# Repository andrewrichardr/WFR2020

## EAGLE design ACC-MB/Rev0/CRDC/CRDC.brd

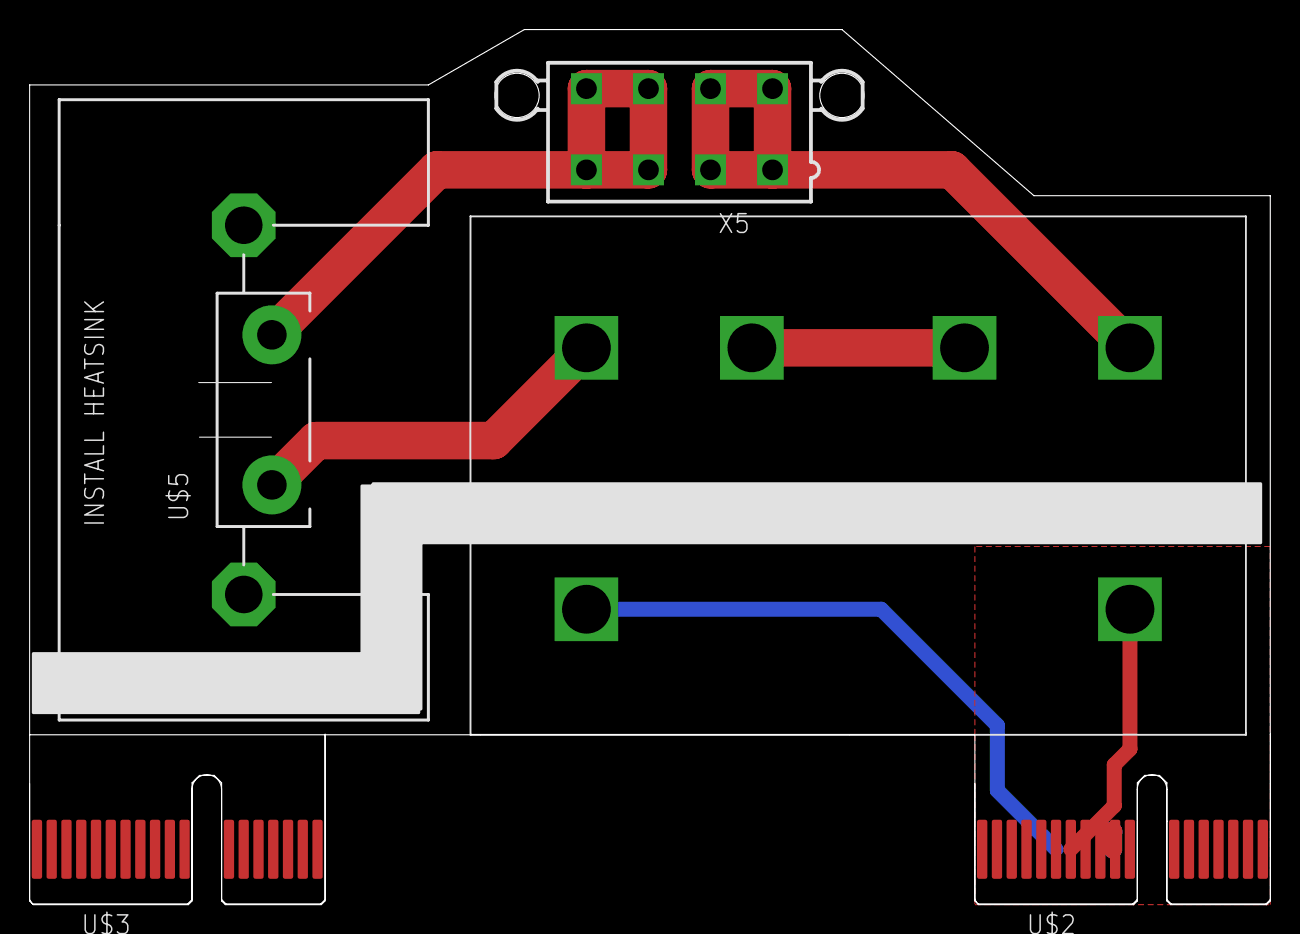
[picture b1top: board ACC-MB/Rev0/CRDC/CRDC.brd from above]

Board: 2 copper layers, 84.0 x 59.2 mm, 5 parts (0 on the bottom side), 6 nets.

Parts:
U$1: G7L
U$2, U$3: PCIE-36-EDGE; PCI-E_SLOT_36
U$5: TO247RESISTORHEATINK; _CUSTOM_TO-247-2V
X5: 5566-8

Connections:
HV+_WET: U$5.2, X5.3, X5.4, X5.7, X5.8
unnamed: U$1.1, U$2.A1, U$2.A2, U$2.A3, U$2.A4, U$2.A5, U$2.A6, U$2.A7, U$2.A8, U$2.A9, U$2.A10, U$2.A11, U$2.A12, U$2.A13, U$2.A14, U$2.A15, U$2.A16, U$2.A17, U$2.A18
unnamed: U$1.0, U$2.B1, U$2.B2, U$2.B3, U$2.B4, U$2.B5, U$2.B6, U$2.B7, U$2.B8, U$2.B9, U$2.B10, U$2.B11, U$2.B12, U$2.B13, U$2.B14, U$2.B15, U$2.B16, U$2.B17, U$2.B18
unnamed: U$1.8, U$5.1
unnamed: U$1.4, U$1.6
V+: U$1.2, X5.1, X5.2, X5.5, X5.6

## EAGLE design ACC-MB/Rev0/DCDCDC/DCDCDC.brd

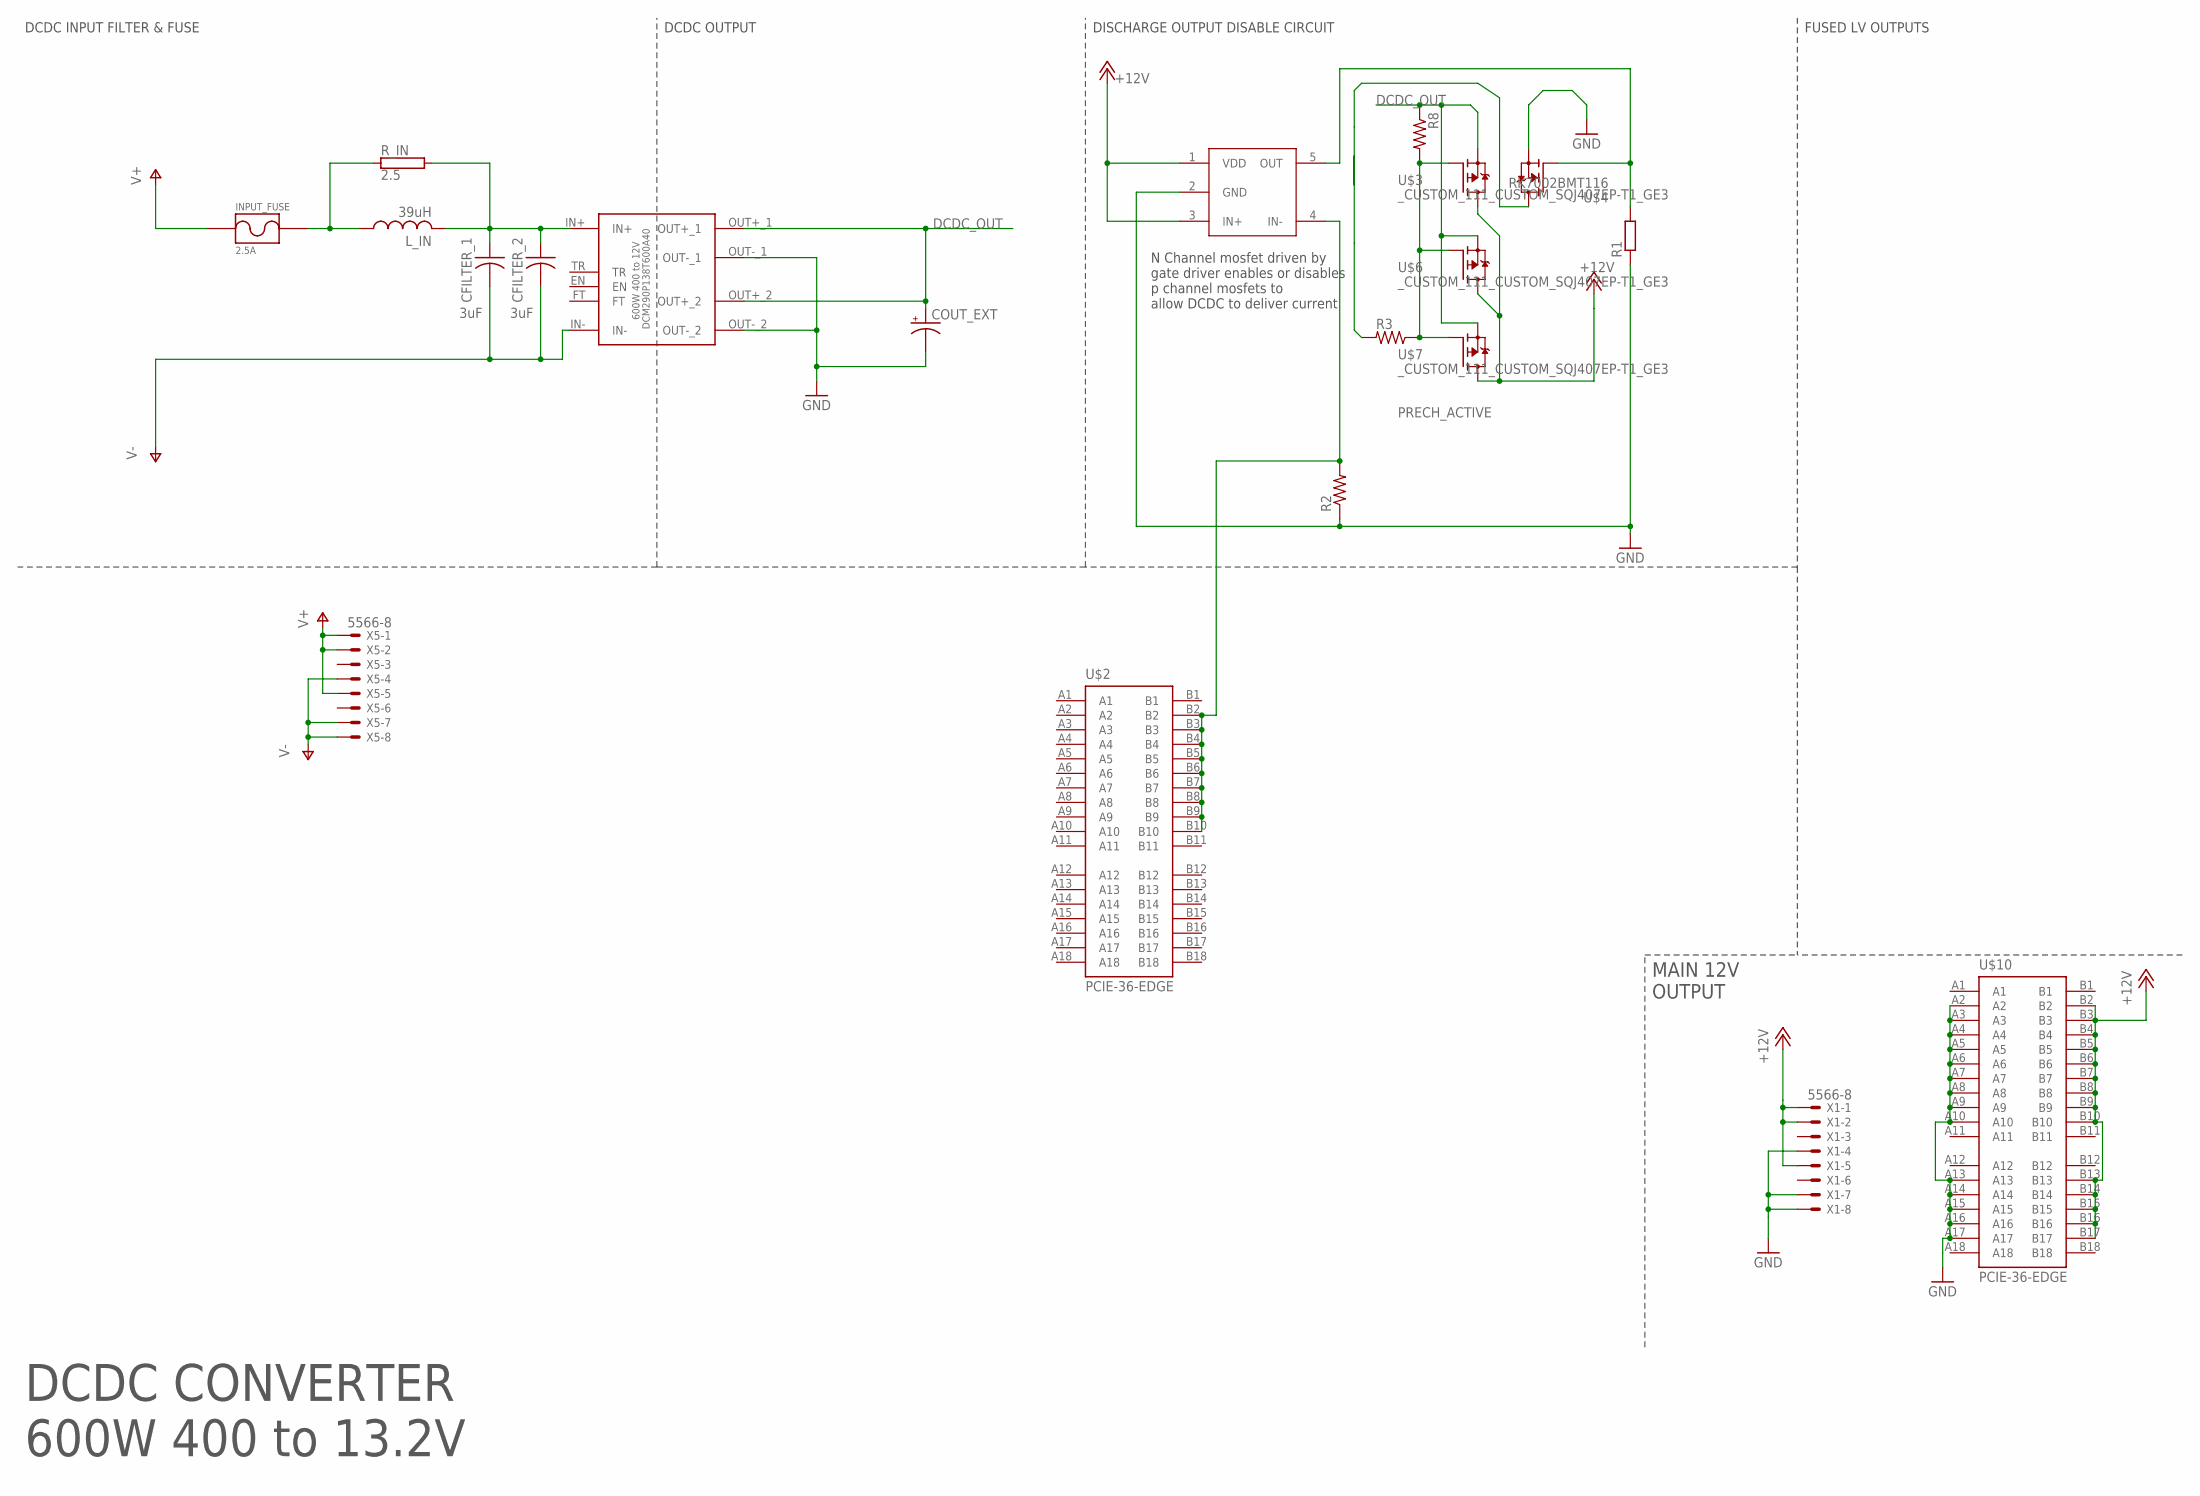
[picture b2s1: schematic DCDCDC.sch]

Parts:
CFILTER_1, CFILTER_2: 3uF; CERALINK_FA3
COUT_EXT: CPOL-USE7.5-16; E7,5-16
DCM290P138T600A40: 600W 400 to 12V; VICOR_CHIP_HEATSINK
INPUT_FUSE: 2.5A; _CUSTOM_PARTS_LF_885
L_IN: 39uH; L_1510_NONSTANDARD
R1: R-EU_R0805; R0805
R2, R3, R8: R-US_R0805; R0805
R_IN: 2.5; TO-247-2V
U$2, U$10: PCIE-36-EDGE; PCI-E_SLOT_36
U$3, U$6, U$7: _CUSTOM_111_CUSTOM_SQJ407EP-T1_GE3; _CUSTOM_111_CUSTOM_TRANS_SIRA90DP-T1-GE3
U$4: RK7002BMT116; SOT23
U$5: UCC27511AQDBVRQ1; SOT23-5L
X1, X5: 5566-8

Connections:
+12V: U$3.5 (D), U$5.1 (VDD), U$5.3 (IN+), U$6.5 (D), U$7.5 (D), U$10.B2, U$10.B3, U$10.B4, U$10.B5, U$10.B6, U$10.B7, U$10.B8, U$10.B9, U$10.B10, U$10.B13, U$10.B14, U$10.B15, U$10.B16, U$10.B17
DCDC_OUT: COUT_EXT.+, DCM290P138T600A40.OUT+_1, DCM290P138T600A40.OUT+_2, R8.1, U$3.1 (S), U$3.2 (S), U$3.3 (S), U$6.1 (S), U$6.2 (S), U$6.3 (S), U$7.1 (S), U$7.2 (S), U$7.3 (S)
GND: COUT_EXT.-, DCM290P138T600A40.OUT-_1, DCM290P138T600A40.OUT-_2, R1.1, R2.1, U$4.2 (S), U$5.2 (GND), U$10.A2, U$10.A3, U$10.A4, U$10.A5, U$10.A6, U$10.A7, U$10.A8, U$10.A9, U$10.A10, U$10.A13, U$10.A14, U$10.A15, U$10.A16, U$10.A17
unnamed: R3.1, R8.2, U$3.4 (G), U$6.4 (G), U$7.4 (G)
unnamed: R1.2, U$4.1 (G), U$5.5 (OUT)
unnamed: CFILTER_1.P$1 (1), CFILTER_2.P$1 (1), DCM290P138T600A40.IN+, L_IN.P$2 (2), R_IN.2
unnamed: R3.2, U$4.3 (D)
unnamed: X1.1, X1.2, X1.5
unnamed: X1.4, X1.7, X1.8
PRECH_ACTIVE: R2.2, U$2.B2, U$2.B3, U$2.B4, U$2.B5, U$2.B6, U$2.B7, U$2.B8, U$2.B9, U$2.B10, U$5.4 (IN-)
V+: INPUT_FUSE.P$1, X5.1, X5.2, X5.5
V+_FUSED: INPUT_FUSE.P$2, L_IN.P$1 (1), R_IN.1
V-: CFILTER_1.P$2 (2), CFILTER_2.P$2 (2), DCM290P138T600A40.IN-, X5.4, X5.7, X5.8

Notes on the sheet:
DCDC CONVERTER 600W 400 to 13.2V
DISCHARGE OUTPUT DISABLE CIRCUIT
FUSED LV OUTPUTS
MAIN 12V OUTPUT
DCDC OUTPUT
DCDC INPUT FILTER & FUSE
N Channel mosfet driven by gate driver enables or disables p channel mosfets to allow DCDC to deliver current

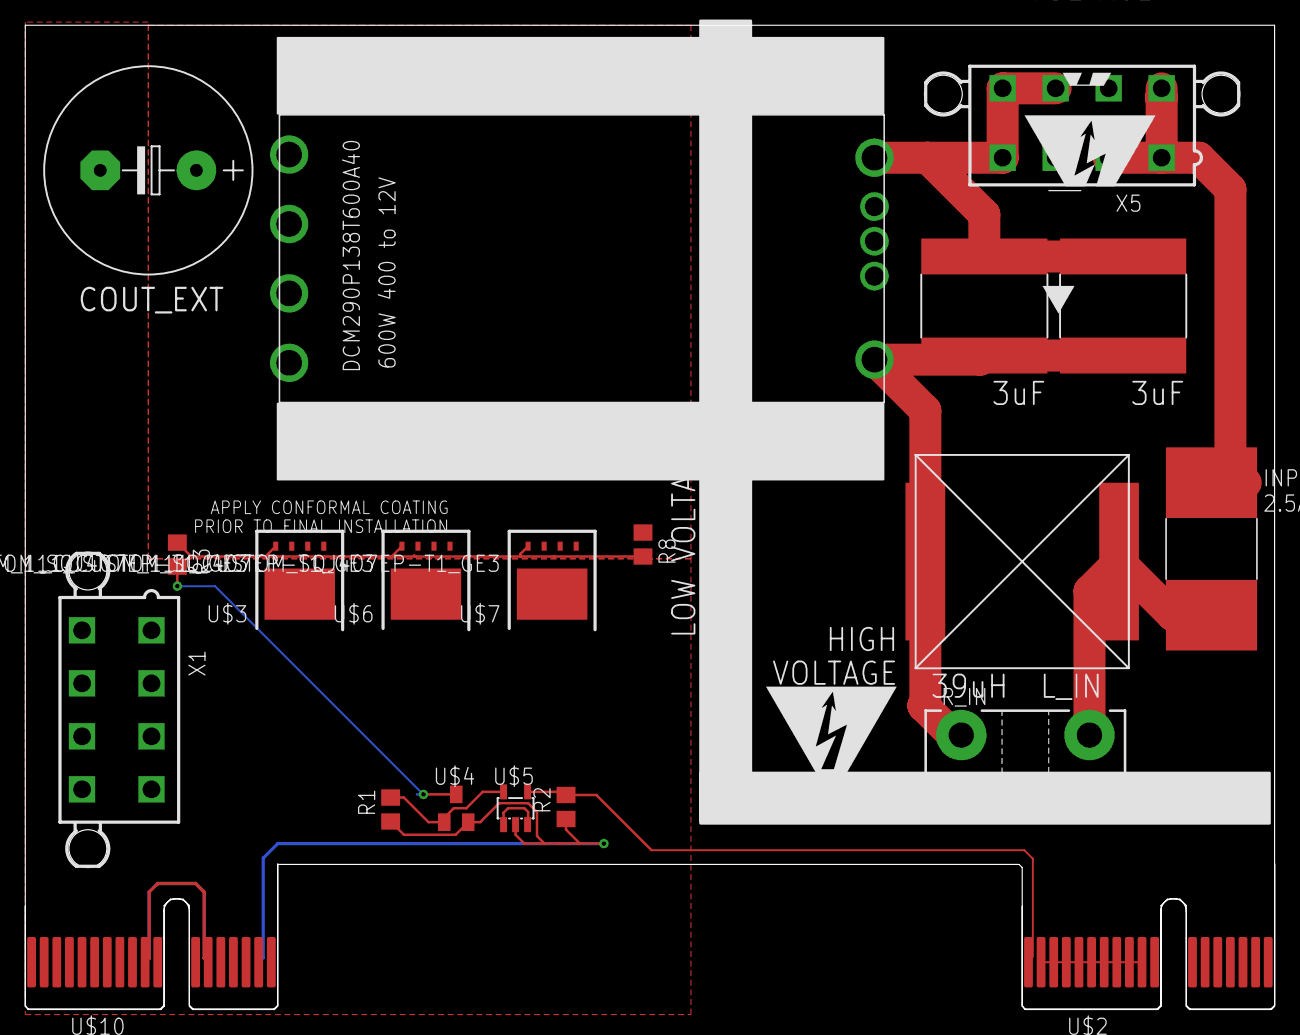
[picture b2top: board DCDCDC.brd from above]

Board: 2 copper layers, 99.0 x 78.0 mm, 20 parts (0 on the bottom side), 13 nets.

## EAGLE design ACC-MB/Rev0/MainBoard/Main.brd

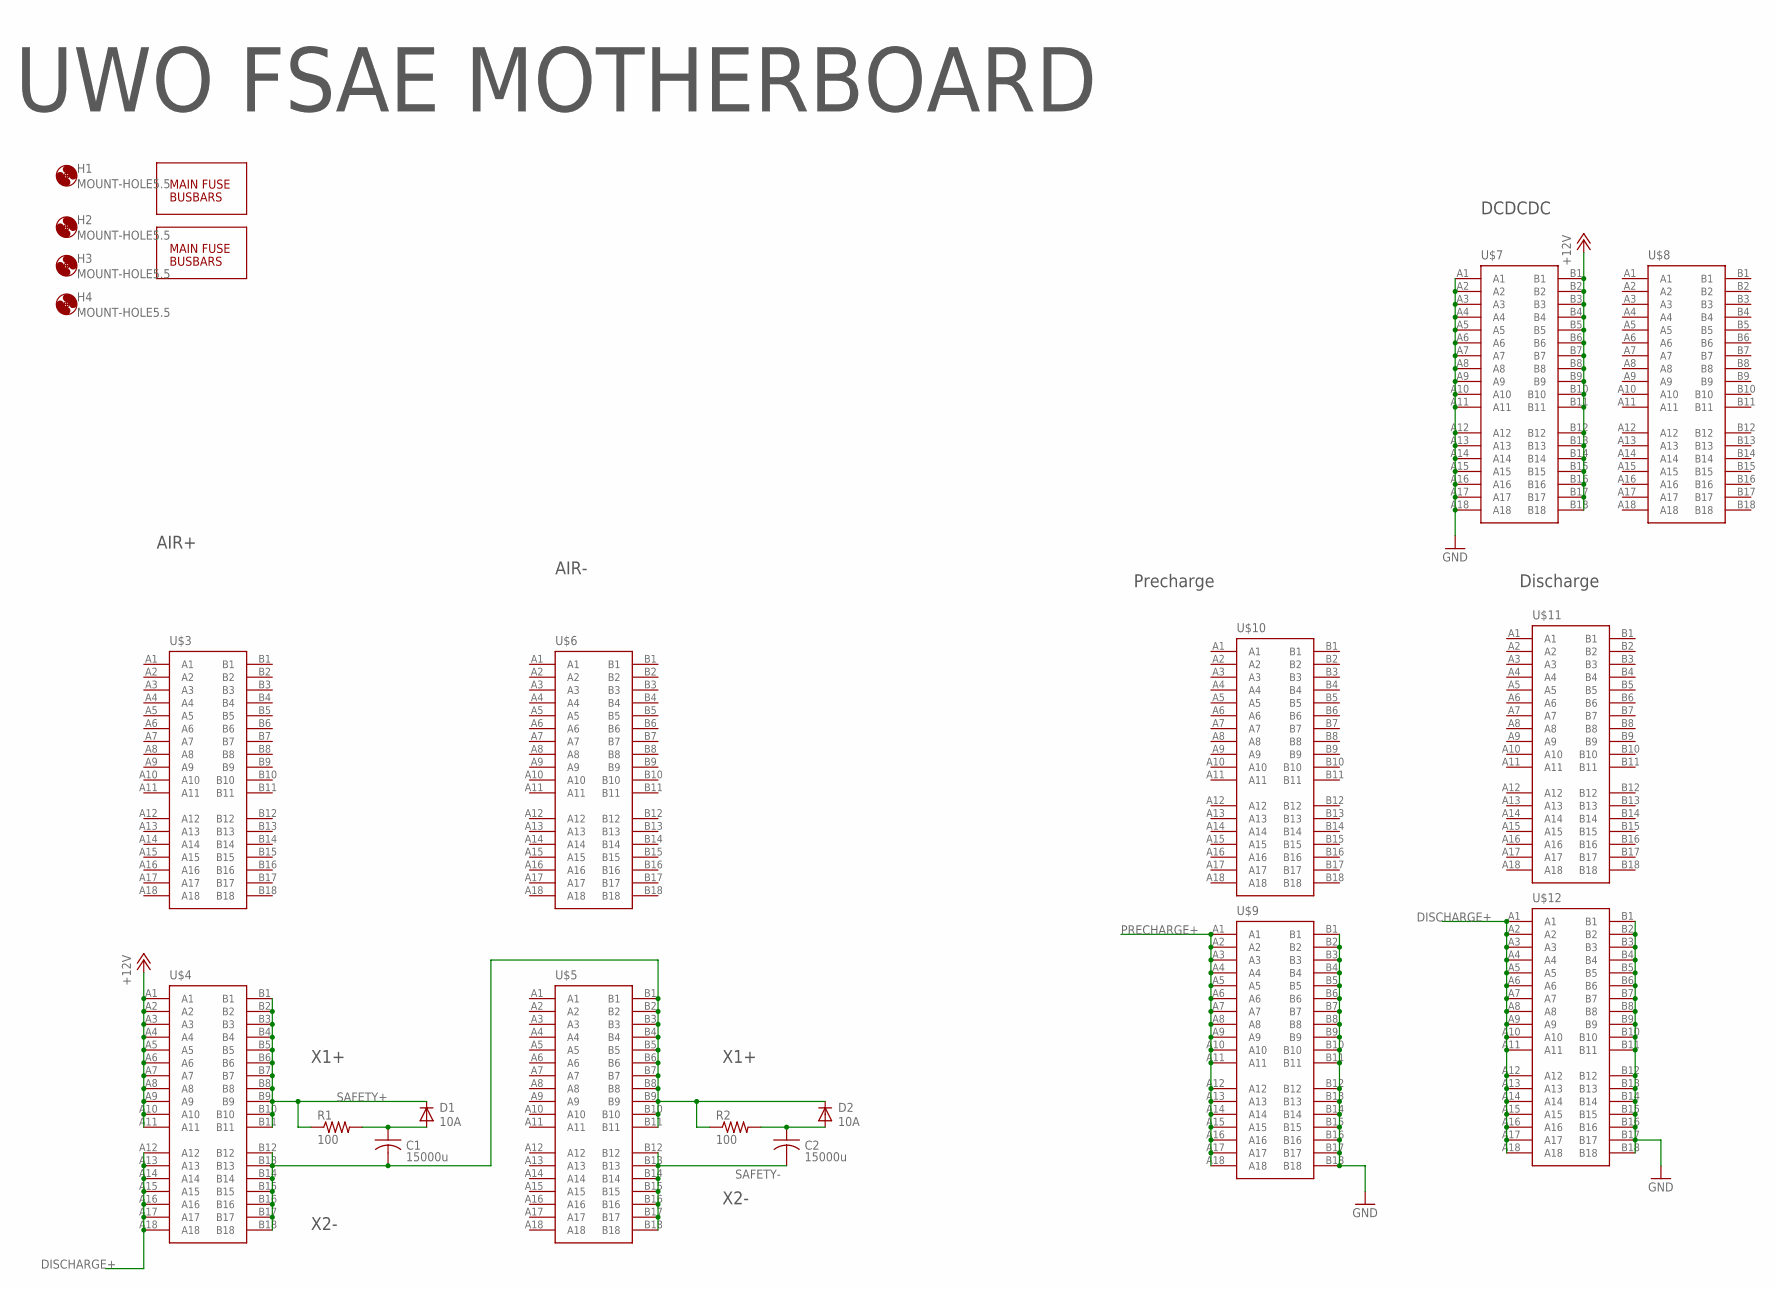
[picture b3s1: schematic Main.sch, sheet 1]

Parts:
C1, C2: 15000u; CAPPRD750W65D1800H3700B
D1, D2: 10A; DIOAD1570W120L850D500B
H1, H2, H3, H4: MOUNT-HOLE5.5; 5,5
R1, R2: 100; RESAD976W63L650D250B
U$1, U$2: FUSE_HOLDER
U$3, U$4, U$5, U$6, U$7, U$8, U$9, U$10, U$11, U$12: PCIE-36-CONN; PCI-E-36-CONN

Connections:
+12V: U$4.A1, U$4.A2, U$4.A3, U$4.A4, U$4.A5, U$4.A6, U$4.A7, U$4.A8, U$4.A9, U$4.A10, U$4.A11, U$7.B1, U$7.B2, U$7.B3, U$7.B4, U$7.B5, U$7.B6, U$7.B7, U$7.B8, U$7.B9, U$7.B10, U$7.B11, U$7.B12, U$7.B13, U$7.B14, U$7.B15, U$7.B16, U$7.B17, U$7.B18; also elsewhere on the board
DISCHARGE+: U$4.A12, U$4.A13, U$4.A14, U$4.A15, U$4.A16, U$4.A17, U$4.A18, U$12.A1, U$12.A2, U$12.A3, U$12.A4, U$12.A5, U$12.A6, U$12.A7, U$12.A8, U$12.A9, U$12.A10, U$12.A11, U$12.A12, U$12.A13, U$12.A14, U$12.A15, U$12.A16, U$12.A17, U$12.A18
GND: U$7.A1, U$7.A2, U$7.A3, U$7.A4, U$7.A5, U$7.A6, U$7.A7, U$7.A8, U$7.A9, U$7.A10, U$7.A11, U$7.A12, U$7.A13, U$7.A14, U$7.A15, U$7.A16, U$7.A17, U$7.A18, U$9.B1, U$9.B2, U$9.B3, U$9.B4, U$9.B5, U$9.B6, U$9.B7, U$9.B8, U$9.B9, U$9.B10, U$9.B11, U$9.B12, U$9.B13, U$9.B14, U$9.B15, U$9.B16, U$9.B17, U$9.B18, U$12.B1, U$12.B2, U$12.B3, U$12.B4, U$12.B5, U$12.B6, U$12.B7, U$12.B8, U$12.B9, U$12.B10, U$12.B11, U$12.B12, U$12.B13, U$12.B14, U$12.B15, U$12.B16, U$12.B17, U$12.B18; also elsewhere on the board
unnamed: C1.1, D1.2 (A), R1.2
unnamed: C1.2, D2.1 (C), R2.1, U$4.B12, U$4.B13, U$4.B14, U$4.B15, U$4.B16, U$4.B17, U$4.B18, U$5.B1, U$5.B2, U$5.B3, U$5.B4, U$5.B5, U$5.B6, U$5.B7, U$5.B8, U$5.B9, U$5.B10, U$5.B11
unnamed: C2.1, D2.2 (A), R2.2
PRECHARGE+: U$9.A1, U$9.A2, U$9.A3, U$9.A4, U$9.A5, U$9.A6, U$9.A7, U$9.A8, U$9.A9, U$9.A10, U$9.A11, U$9.A12, U$9.A13, U$9.A14, U$9.A15, U$9.A16, U$9.A17, U$9.A18; also elsewhere on the board
SAFETY+: D1.1 (C), R1.1, U$4.B1, U$4.B2, U$4.B3, U$4.B4, U$4.B5, U$4.B6, U$4.B7, U$4.B8, U$4.B9, U$4.B10, U$4.B11; also elsewhere on the board
SAFETY-: C2.2, U$5.B12, U$5.B13, U$5.B14, U$5.B15, U$5.B16, U$5.B17, U$5.B18; also elsewhere on the board

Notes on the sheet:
UWO FSAE MOTHERBOARD
DCDCDC
AIR-
AIR+
Precharge
Discharge
X1+
X2-

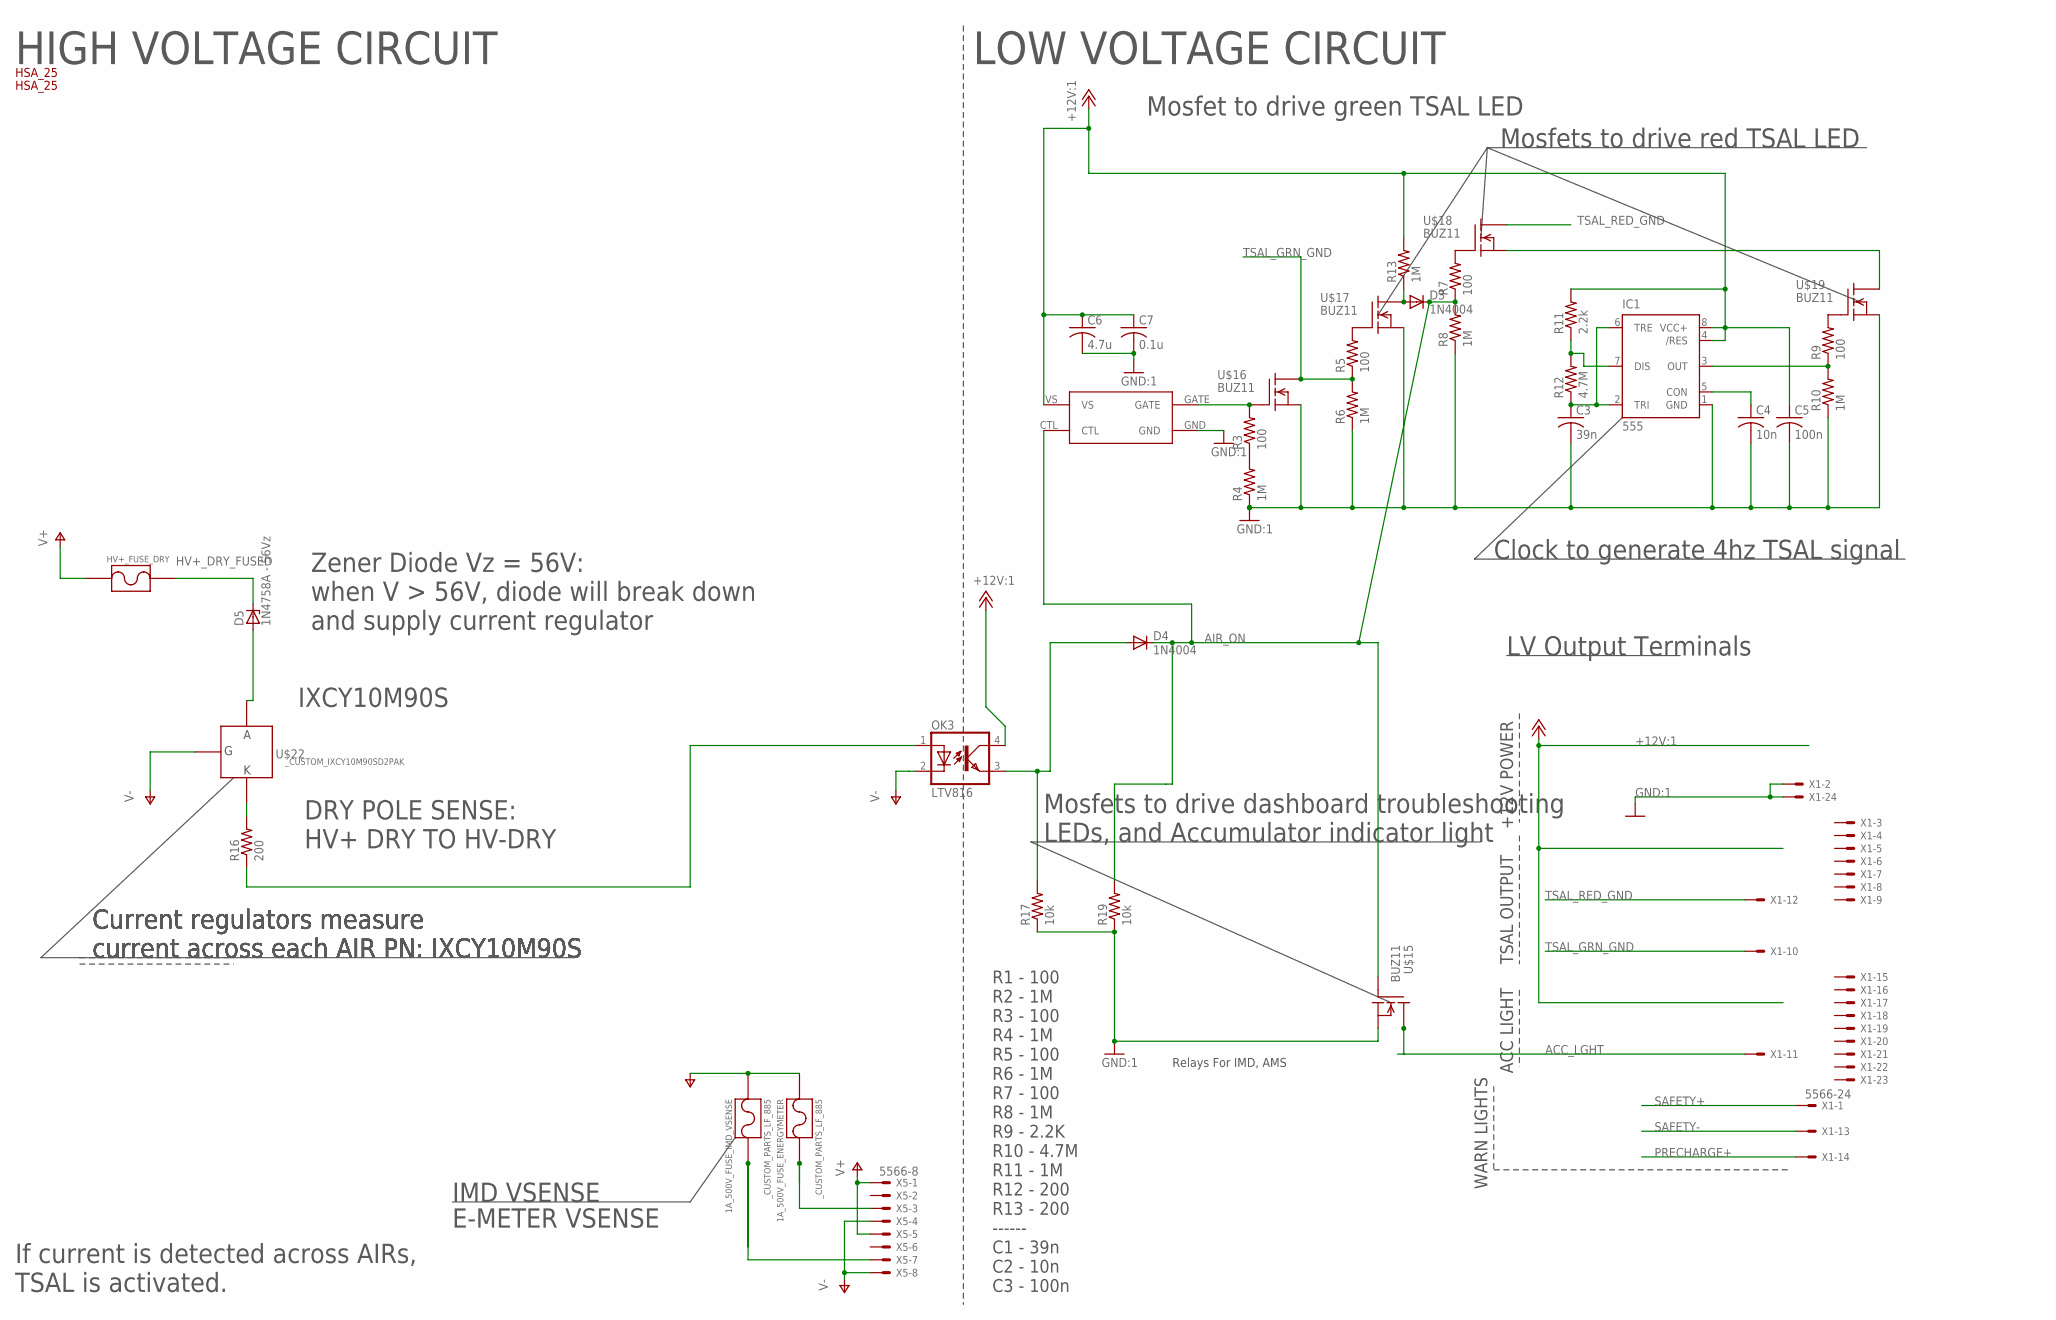
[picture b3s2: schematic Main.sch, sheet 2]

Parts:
1A_500V_FUSE_ENERGYMETER, 1A_500V_FUSE_IMD_VSENSE: _CUSTOM_PARTS_LF_885
C3: 39n; C0805
C4: 10n; C0805
C5: 100n; C0805
C6: 4.7u; C0805
C7: 0.1u; C0805
D3, D4: 1N4004; DO41-10
D5: 1N4758A - 56Vz; ZDIO12.5
HV+_FUSE_DRY: _CUSTOM_PARTS_LF_885
IC1: 555; DIP08
OK3: LTV816; DIL04
R3, R5, R7, R9: 100; R0805:1
R4, R6, R8, R10, R13: 1M; R0805:1
R11: 2.2k; R0805:1
R12: 4.7M; R0805:1
R16: 200; R2010
R17, R19: 10k; R0805:1
U$15, U$16, U$17, U$18, U$19: BUZ11; TO220
U$22: _CUSTOM_IXCY10M90SD2PAK; TO228P991X238-3
U$23: MIC4417; PDM_2019_REVB_MIC4416YM4-TR
U$24, U$25: HSA25; HSA_25_FOOT
X1: 5566-24
X5: 5566-8

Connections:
+12V: C5.1, C6.1, C7.1, IC1.4 (/RES), IC1.8 (VCC+), OK3.4 (COL), R11.2, R13.2, U$23.VS; also elsewhere on the board
ACC_LGHT: U$15.2 (D), X1.11
AIR_ON: D3.C, D4.C, R7.1, R8.2, R19.2, U$15.1 (G), U$23.CTL
GND: C3.2, C4.2, C5.2, C6.2, C7.2, IC1.1 (GND), R4.1, R6.1, R8.1, R10.1, R17.1, R19.1, U$15.3 (S), U$16.3 (S), U$17.3 (S), U$19.3 (S), U$23.GND, X1.2, X1.24; also elsewhere on the board
HV+_DRY_FUSED: D5.C, HV+_FUSE_DRY.P$1
unnamed: C4.1, IC1.5 (CON)
unnamed: 1A_500V_FUSE_ENERGYMETER.P$2, X5.3
unnamed: IC1.7 (DIS), R11.1, R12.2
unnamed: IC1.3 (OUT), R9.1, R10.2
unnamed: C3.1, IC1.2 (TRI), IC1.6 (TRE), R12.1
unnamed: R3.1, R4.2
unnamed: R3.2, U$16.1 (G), U$23.GATE
unnamed: R5.2, U$17.1 (G)
unnamed: U$18.3 (S), U$19.2 (D)
unnamed: D4.A, OK3.3 (EMIT), R17.2
unnamed: D3.A, R13.1, U$17.2 (D)
unnamed: R7.2, U$18.1 (G)
unnamed: R9.2, U$19.1 (G)
unnamed: 1A_500V_FUSE_IMD_VSENSE.P$2, X5.7
unnamed: R16.2, U$22.2 (K)
unnamed: D5.A, U$22.3 (A)
unnamed: OK3.1 (A), R16.1
PRECHARGE+: X1.14; also elsewhere on the board
SAFETY+: X1.1; also elsewhere on the board
SAFETY-: X1.13; also elsewhere on the board
TSAL_GRN_GND: R5.1, R6.2, U$16.2 (D), X1.10
TSAL_RED_GND: U$18.2 (D), X1.12
V+: HV+_FUSE_DRY.P$2, X5.1, X5.5
V-: 1A_500V_FUSE_ENERGYMETER.P$1, 1A_500V_FUSE_IMD_VSENSE.P$1, OK3.2 (C), U$22.1 (G), X5.4, X5.8

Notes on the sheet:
HIGH VOLTAGE CIRCUIT
LOW VOLTAGE CIRCUIT
TSAL OUTPUT
ACC LIGHT
WARN LIGHTS
Current regulators measure current across each AIR PN: IXCY10M90S
Mosfets to drive dashboard troubleshooting LEDs, and Accumulator indicator light
Clock to generate 4hz TSAL signal
Mosfets to drive red TSAL LED
Mosfet to drive green TSAL LED
+12V POWER
If current is detected across AIRs, TSAL is activated.
LV Output Terminals
R1 - 100 R2 - 1M R3 - 100 R4 - 1M R5 - 100 R6 - 1M R7 - 100 R8 - 1M R9 - 2.2K R10 - 4.7M R11 - 1M R12 - 200 R13 - 200 ------ C1 - 39n C2 - 10n C3 - 100n
E-METER VSENSE
IMD VSENSE
DRY POLE SENSE: HV+ DRY TO HV-DRY
Relays For IMD, AMS
IXCY10M90S
Zener Diode Vz = 56V: when V > 56V, diode will break down and supply current regulator

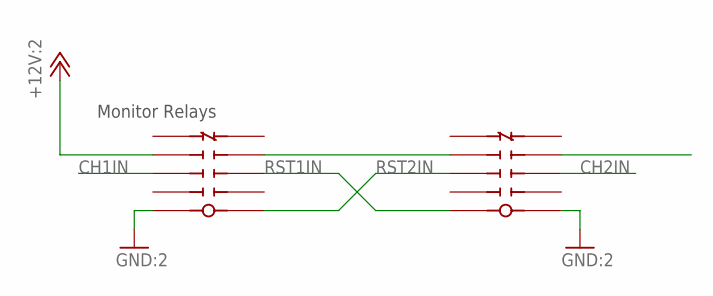
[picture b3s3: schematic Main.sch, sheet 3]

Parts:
U$13, U$14: SR4M4012_TE; SR4M4012_FOOT

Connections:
+12V: U$13.NOA3; also elsewhere on the board
CH1IN: U$13.NOA2
CH2IN: U$14.NOB2
GND: U$13.COIL+, U$14.COIL-; also elsewhere on the board
unnamed: U$13.NOB3, U$14.NOA3
RST1IN: U$13.NOB2, U$14.COIL+
RST2IN: U$13.COIL-, U$14.NOA2

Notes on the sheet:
Monitor Relays

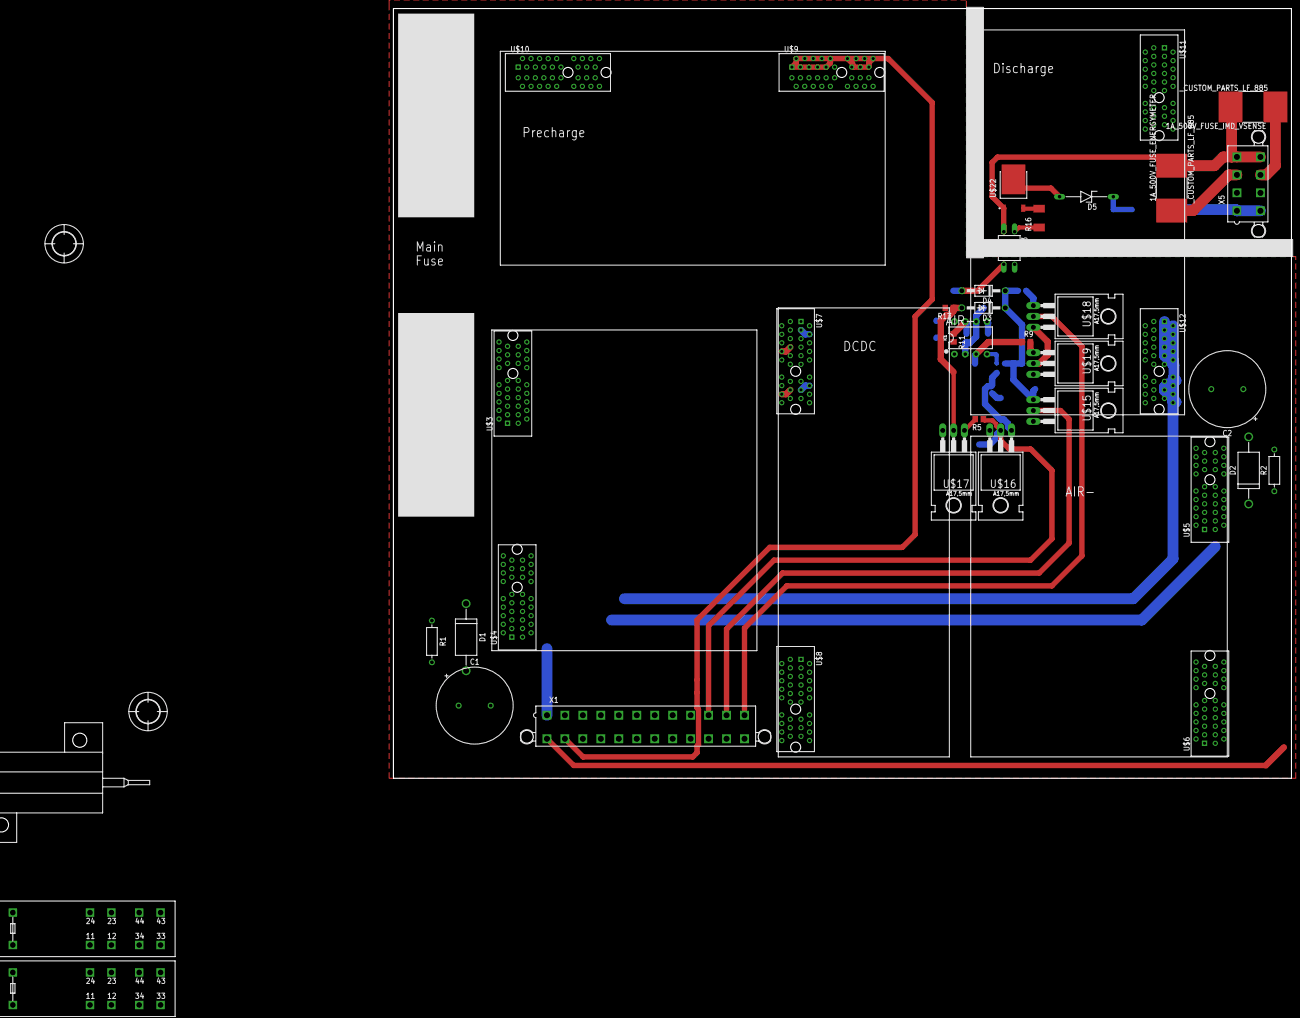
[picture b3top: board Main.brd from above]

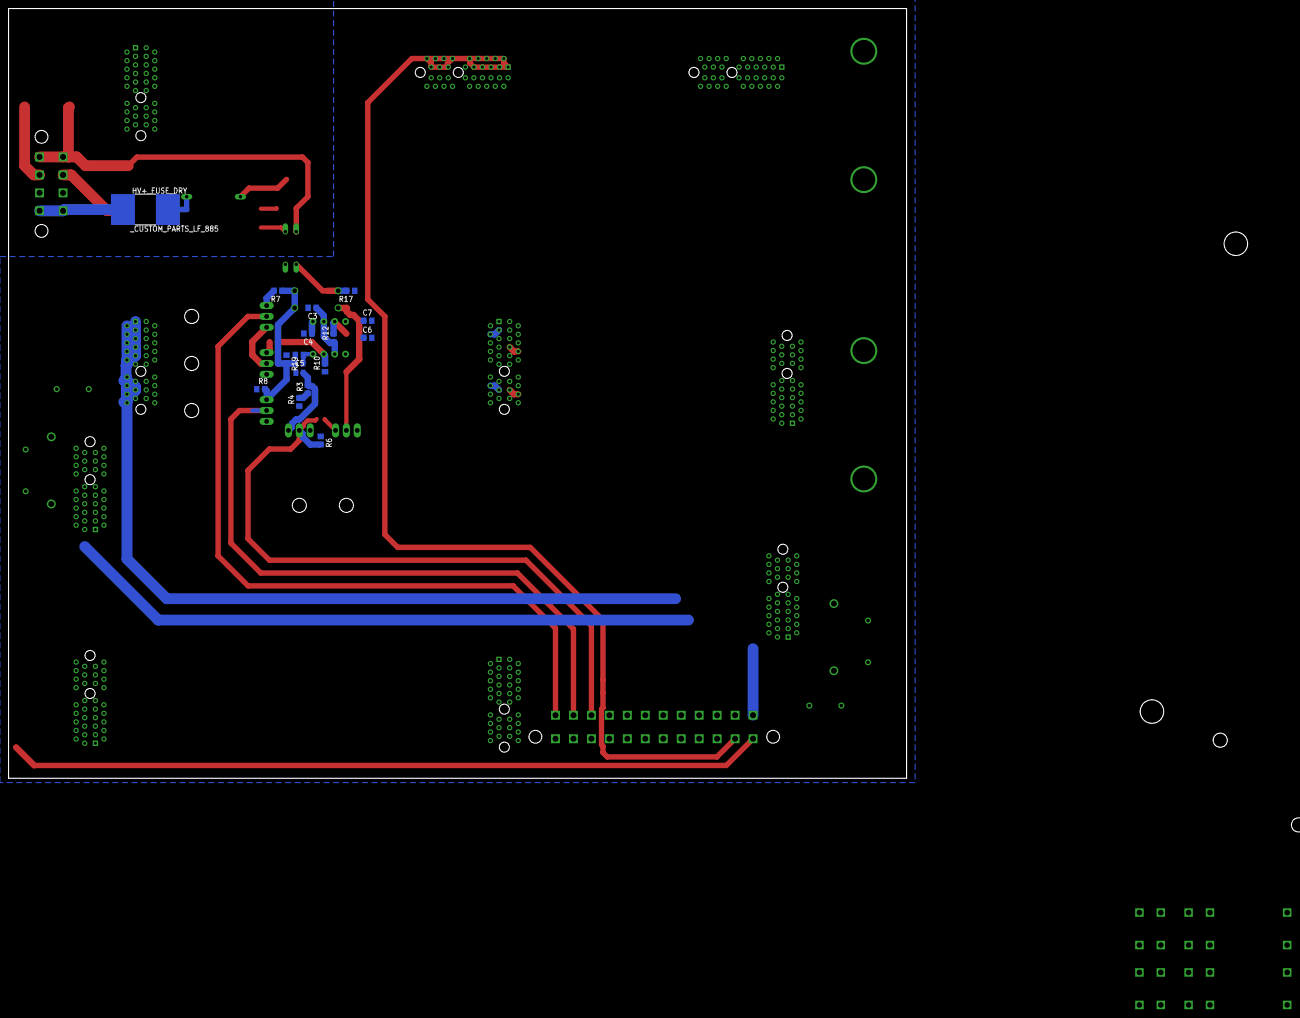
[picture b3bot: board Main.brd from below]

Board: 2 copper layers, 210.0 x 180.0 mm, 62 parts (16 on the bottom side), 36 nets.

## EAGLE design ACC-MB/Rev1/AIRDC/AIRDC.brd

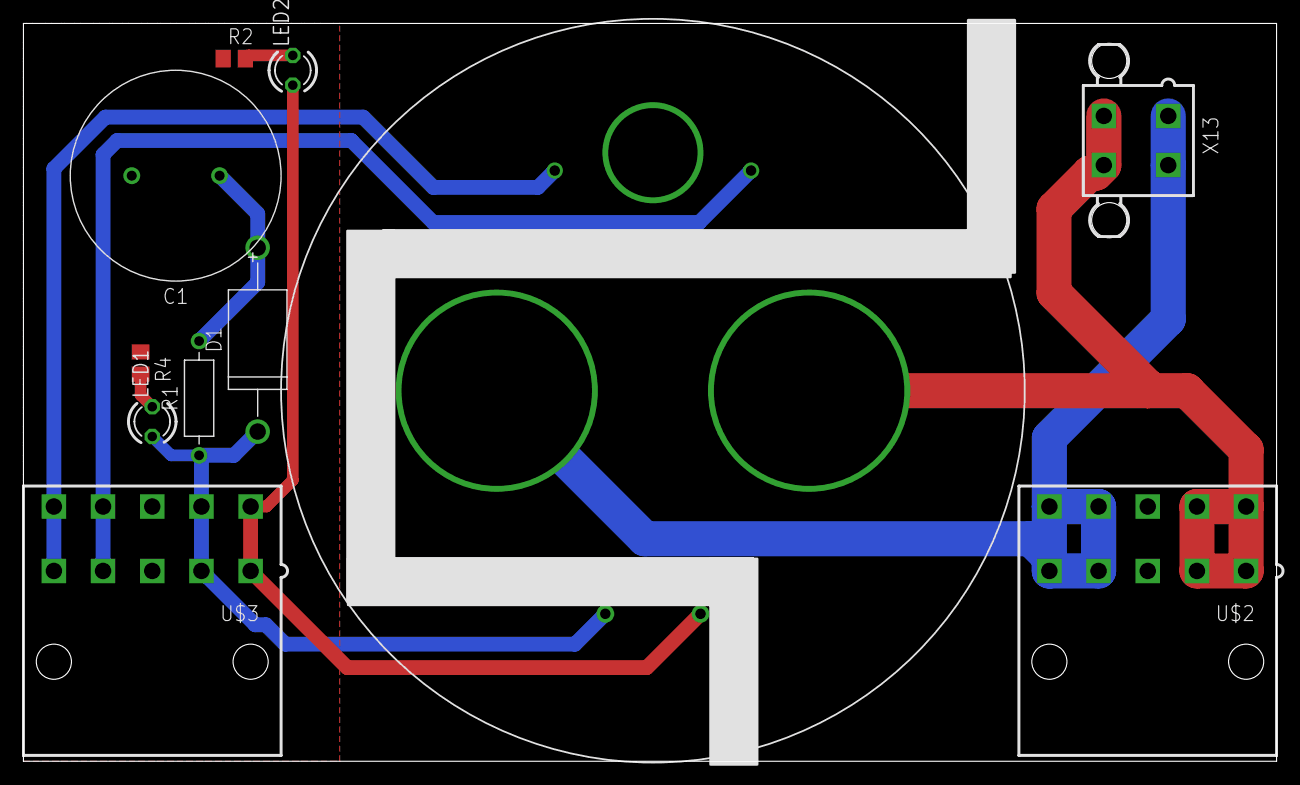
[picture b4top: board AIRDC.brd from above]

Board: 2 copper layers, 107.0 x 63.0 mm, 11 parts (0 on the bottom side), 10 nets.

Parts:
C1: 15000u; CAPPRD750W65D1800H3700B
D1: 10A; DIOAD1570W120L850D500B
LED1, LED2: LED3MM
R1: 100; RESAD976W63L650D250B
R2, R4: R0805
U$1: GV224
U$2, U$3: 15-24-6100
X13: 5566-4

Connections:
AUX_A1: U$1.A1, U$2.4, U$2.5, U$2.9, U$2.10, X13.1, X13.2
AUX_A2: U$1.A2, U$2.1, U$2.2, U$2.6, U$2.7, X13.3, X13.4
AUX_T1: U$1.T1, U$3.5, U$3.10
AUX_T2: U$1.T2, U$3.4, U$3.9
COIL_X1: D1.1, LED1.A, R1.1, U$1.X1, U$3.2, U$3.7
COIL_X2: LED2.A, U$1.X2, U$3.1, U$3.6
GND: C1.2, R2.1, R4.1, U$3.3, U$3.8
unnamed: LED2.K, R2.2
unnamed: C1.1, D1.2, R1.2
unnamed: LED1.K, R4.2

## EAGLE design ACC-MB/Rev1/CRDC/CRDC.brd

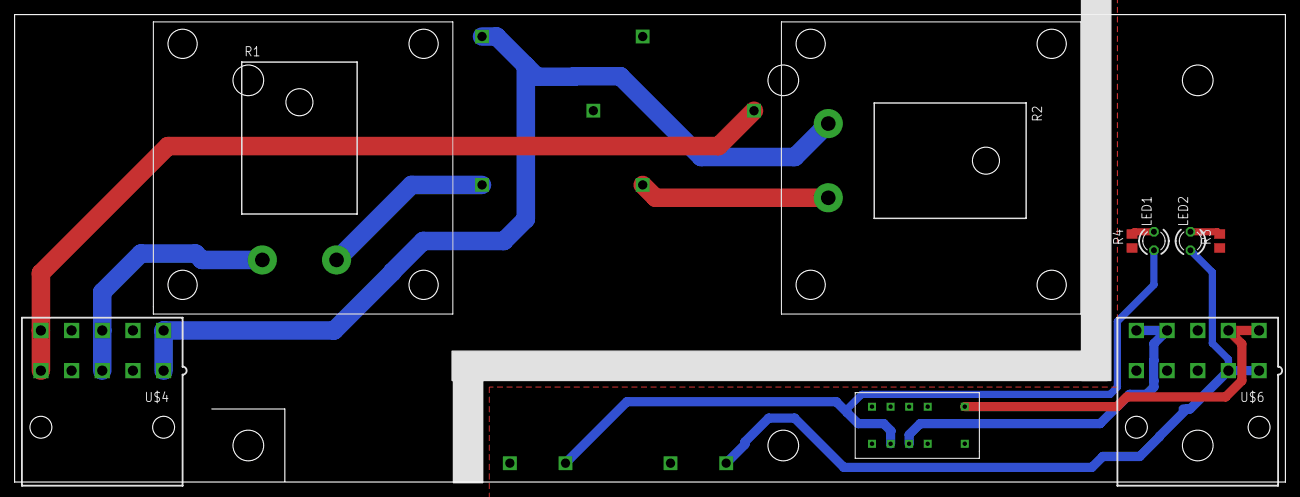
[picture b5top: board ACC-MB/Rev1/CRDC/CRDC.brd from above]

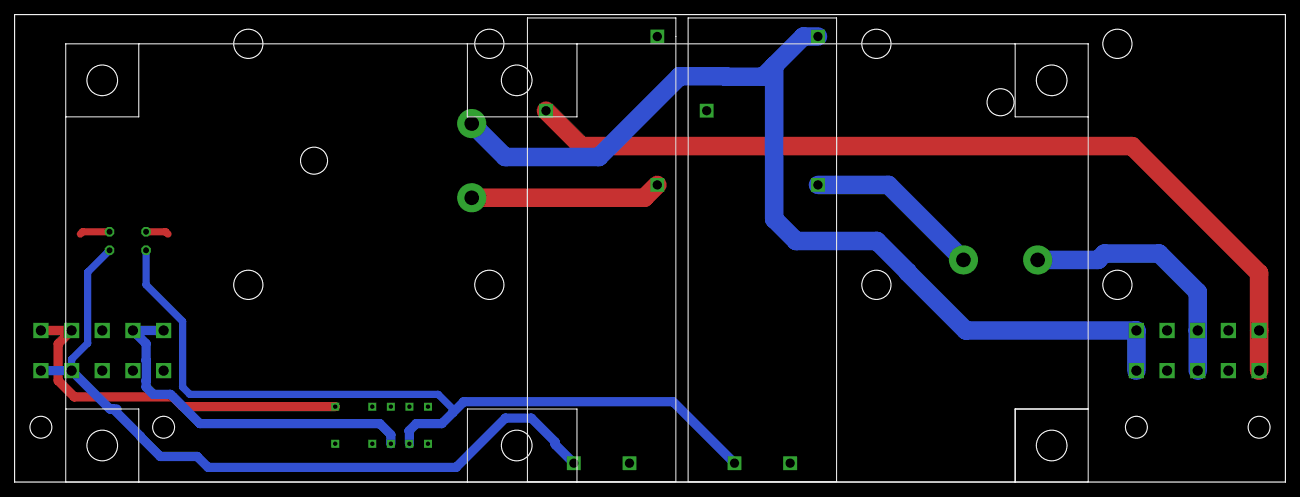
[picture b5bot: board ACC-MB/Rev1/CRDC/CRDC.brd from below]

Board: 2 copper layers, 174.0 x 64.0 mm, 14 parts (3 on the bottom side), 12 nets.

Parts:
LED1, LED2: LED3MM
R1, R2: TO-247-2H
R3, R4: R0805
U$1, U$2: G81C335
U$3: BENDER_IRR155
U$4, U$6: 15-24-6100
U$7: V23079B1203B301
U$8, U$9: HEATSINK40X40X15

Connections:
+12V: U$6.9, U$6.10, U$7.9
DISCHARGE: LED2.A, U$2.L1, U$6.1, U$6.2
GND: R3.1, R4.1, U$1.L2, U$2.L2, U$6.3, U$6.4, U$6.5, U$7.12
HV+_DRY: R2.1, U$1.NO, U$4.1, U$4.6
HV+_WET: R1.1, U$4.3, U$4.8
HV-_DRY_AUX: U$2.NC, U$4.5, U$4.10
unnamed: LED2.K, R3.2
unnamed: R2.2, U$2.COM
unnamed: LED1.K, R4.2
unnamed: R1.2, U$1.COM
PRECHARGE: LED1.A, U$1.L1, U$7.8
PRECHARGE_SIG: U$6.6, U$6.7, U$7.1

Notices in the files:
parts and their libraries:
SparkFun-IC-Special-Function: Licensing: Creative Commons ShareAlike 4.0 International - https://creativecommons.org/licenses/by-sa/4.0
